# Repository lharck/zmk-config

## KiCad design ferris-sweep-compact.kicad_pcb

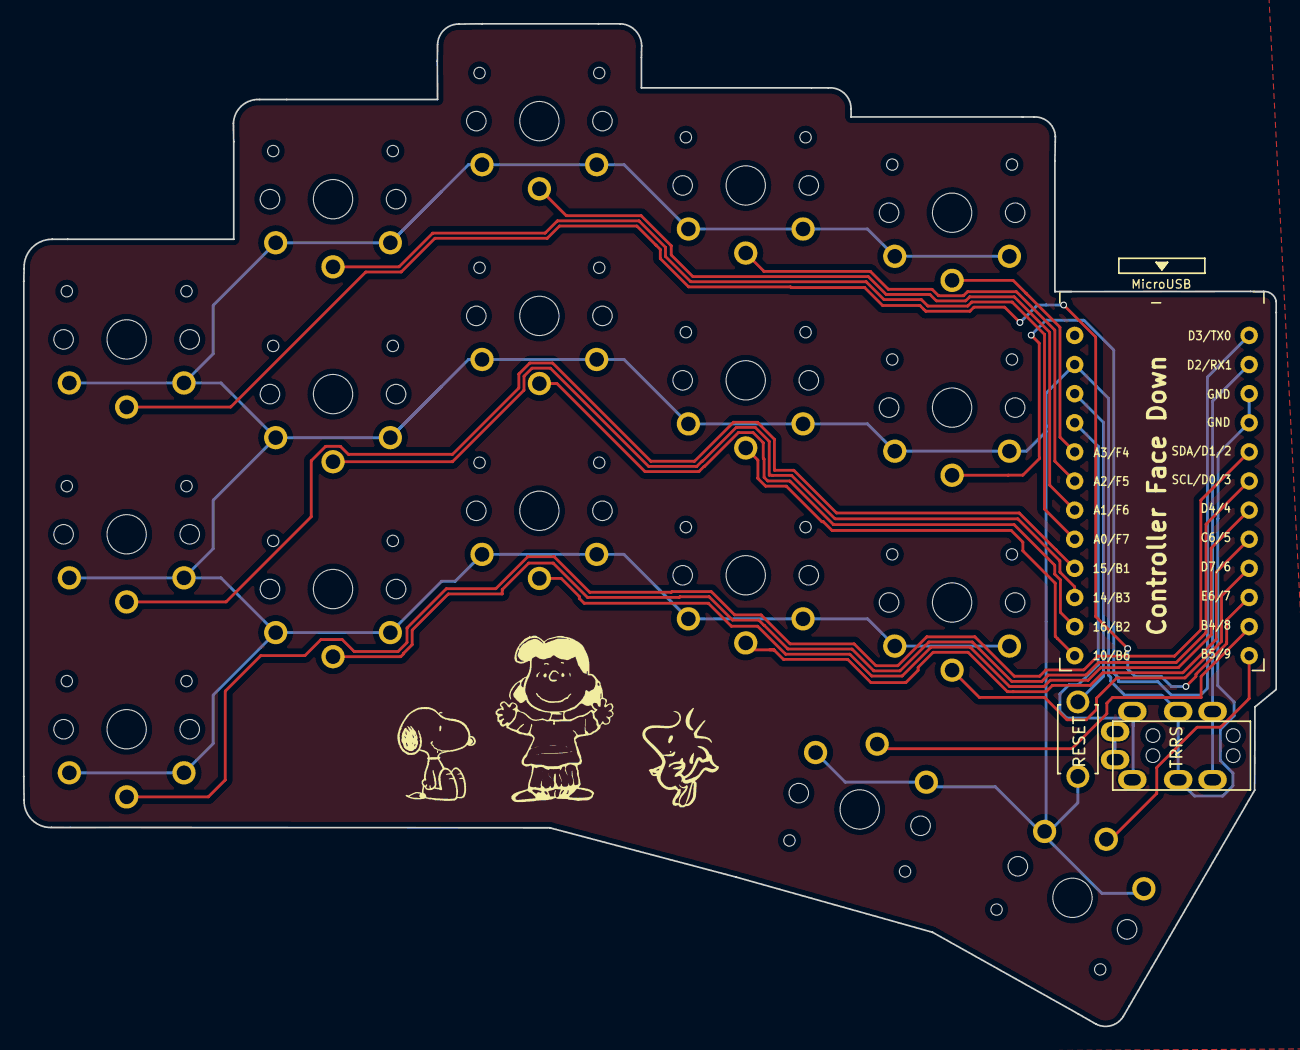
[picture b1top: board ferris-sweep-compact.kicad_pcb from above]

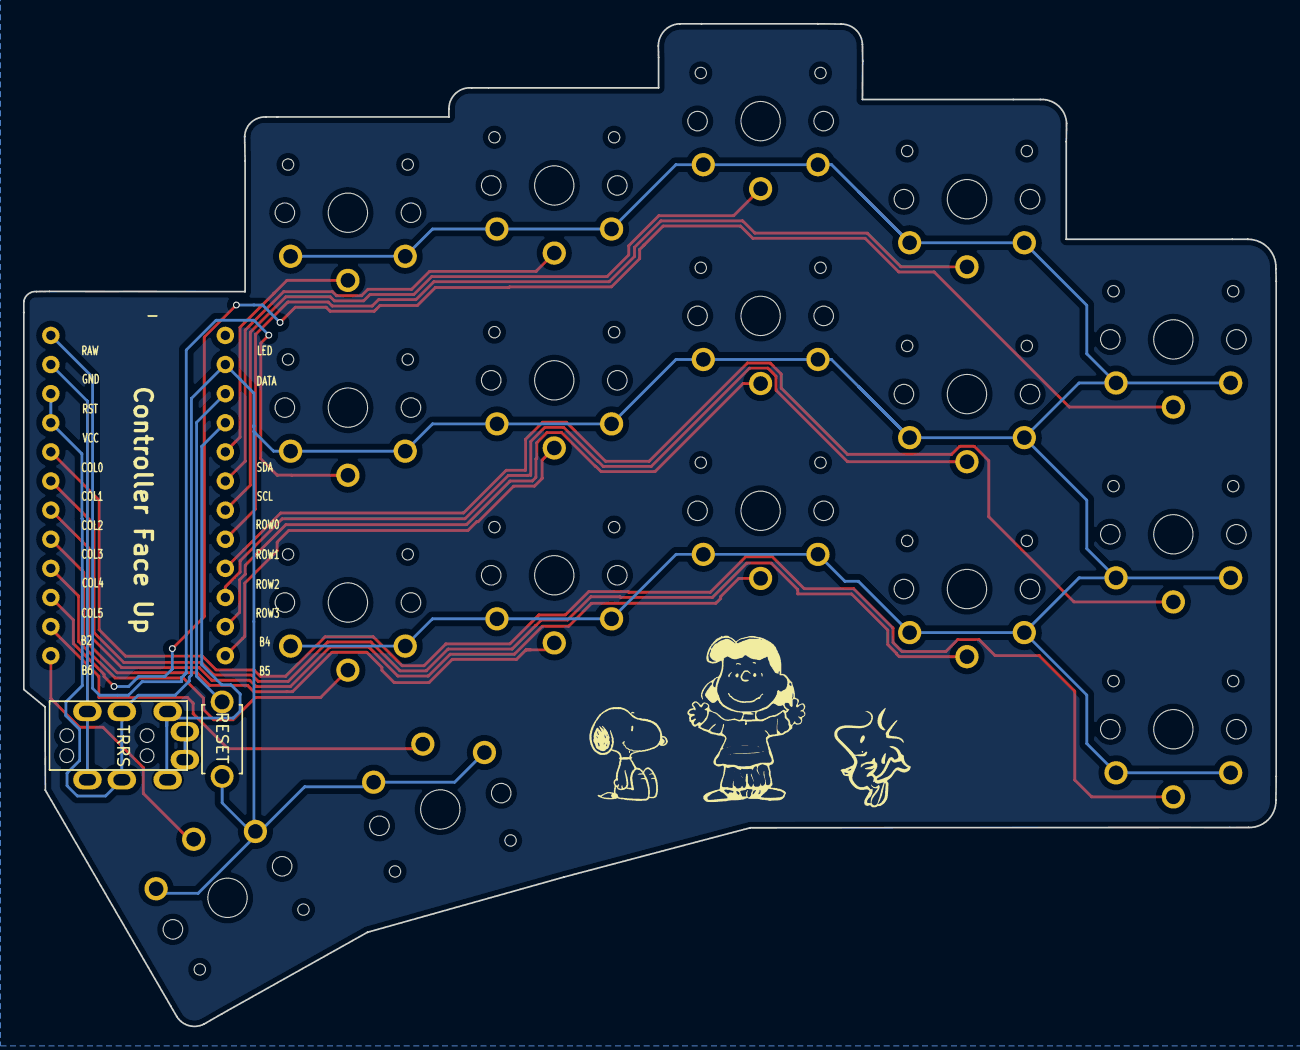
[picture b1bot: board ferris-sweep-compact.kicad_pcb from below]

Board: 2 copper layers, 109.2 x 87.5 mm, 26 parts (5 on the bottom side), 21 nets.

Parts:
02, 02#2: LOGO; woodstock
.1, .1#2: LOGO; Lucy
.., ..#2: LOGO; Snoopy
J1: MJ-4PP-9
RSW1: Val**; ResetSW
SW2, SW3, SW4, SW5, SW6, SW8, SW9, SW10, SW11, SW12, SW14, SW15, SW16, SW17, SW18, SW20, SW21: SW_PUSH; SW_PG1350_reversible_b2
U1: ProMicro; ProMicro_v3

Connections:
GND: J1.C, RSW1.2, SW2.2, SW3.2, SW4.2, SW5.2, SW6.2, SW8.2, SW9.2, SW10.2, SW11.2, SW12.2, SW14.2, SW15.2, SW16.2, SW17.2, SW18.2, SW20.2, SW21.2, U1.3, U1.4, U1.23
LED: SW12.1, U1.1
unnamed: SW20.1, U1.11
unnamed: SW21.1, U1.12
unnamed: SW11.1, U1.13
unnamed: SW10.1, U1.14
SCL: SW15.1, U1.6
SDA: SW14.1, U1.5
VCC: J1.D, U1.21
col0: SW6.1, U1.20
col1: SW5.1, U1.19
col2: SW4.1, U1.18
col3: SW3.1, U1.17
col4: SW8.1, U1.16
col5: SW9.1, U1.15
data: J1.B, U1.2
reset: RSW1.1, U1.22
row0: SW16.1, U1.7
row1: SW17.1, U1.8
row2: SW18.1, U1.9
row3: SW2.1, U1.10

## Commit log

2022-11-03 Initial User Config.
2022-11-03 added pcb source
2022-11-03 Added my keymap
2022-11-03 got rid of rgb
2022-11-03 test
2022-11-03 bug nav layer
2022-11-04 changed combo keys for wasd and gaming layers
2022-11-11 moved symbols around, added alt tab
2022-11-12 changed keymap to match
    http://www.keyboard-layout-editor.com/#/gists/166f92a35a14a2a77350d2218485addb
2022-11-12 added bluetooth support
2022-11-12 typo
2022-11-12 merging firmwares
2022-11-12 made each keyboard split part have their own firmware
2022-11-12 reorganized firmware page in build.yaml
2022-11-12 mouse pr progress (see description) - temporarily commented out adux firmware for faster compile times - added krikun98 pr west.yml
2022-11-12 initial mouse movement code
2022-11-12 include mouse.h
2022-11-12 controls
2022-11-17 updated keymap
2022-11-25 rsst
2022-11-25 arst
2022-11-25 layer macros
2022-11-25 binded num layer
2022-11-25 HOMEROW MODS
2022-11-25 nav layer
2022-11-25 SYMBOL LAYER
2022-11-26 SETTINGS_LAYER
2022-11-26 changed modifiers on nav layer to be normal keycodes
2022-11-26 key press smh
2022-11-26 finish nav layer
2022-11-26 symb layer
2022-11-26 num and funct layers
2022-11-26 funct+ and mousen layer added modifiers to funct layer moved around and added mods to mouse layer
2022-11-26 middle click
2022-11-26 building for all keyboard builds + reset firmware
2022-11-27 inc tapping term ms
2022-11-27 different home mod method
2022-11-27 a dux conf
2022-11-27 adux keymap
2022-11-29 using urob commit
2022-11-29 testing sample keymap
2022-11-29 attempt 2
2022-11-29 test 3
2022-11-29 test 4
2022-11-29 removed unneeded keymaps
2022-11-29 added sweep keymap
2022-11-29 helper
2022-11-29 dtsi files
2022-11-29 combo
2022-11-29 settings
2022-11-29 hecking random z
2022-11-29 hr mods
2022-11-29 changed matrix
2022-11-29 made layers follow urob style
2022-11-29 formating
2022-11-29 esc and tab combos
2022-12-01 combos
2022-12-01 combos part 2
2022-12-01 adux
2022-12-01 moved num pad to semi colon
2022-12-01 had files in wrong folder
2022-12-01 other side home row
2022-12-01 gave me a bit more time to hit combos
2022-12-03 had hml for left side by accident
